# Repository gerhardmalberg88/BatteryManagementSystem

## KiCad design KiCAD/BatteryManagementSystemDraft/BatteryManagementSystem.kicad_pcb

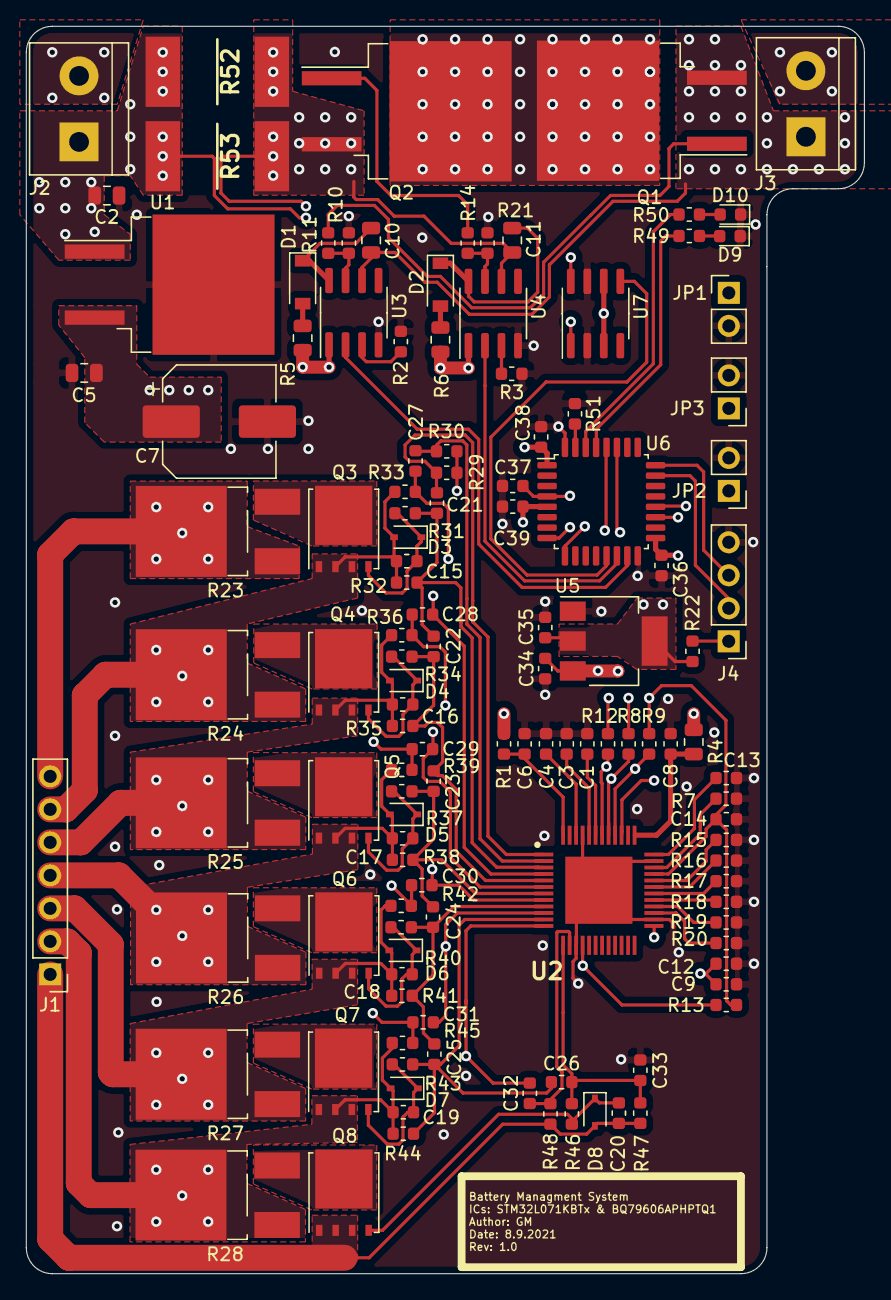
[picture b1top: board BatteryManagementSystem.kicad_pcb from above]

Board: 4 copper layers, 64.5 x 96.0 mm, 124 parts (0 on the bottom side), 82 nets.

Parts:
C1, C3, C4, C9, C12, C13, C14: 2.2uF 10V; C_0603_1608Metric
C2: 0.33uF; C_0805_2012Metric
C5: 0.1uF; C_0805_2012Metric
C6, C8: 330nF 50V; C_0603_1608Metric
C7: 100uF; CP_Elec_8x10.5
C10, C11: 1uF; C_0805_2012Metric
C15, C16, C17, C18, C19, C20: 1nF; C_0603_1608Metric
C21, C22, C23, C24, C25, C26, C27, C28, C29, C30, C31, C32: 1uF; C_0603_1608Metric
C33: 470nF 16V; C_0603_1608Metric
C34, C36, C38, C39: 100nF 10V; C_0603_1608Metric
C35: 10uF 10V; C_0603_1608Metric
C37: 0.1uF; C_0603_1608Metric
D1, D2: 1N6263W-7-F 1A; D_SOD-123
D3, D4, D5, D6, D7, D8: TVS_5.1V; D_SOD-323
D9, D10: LED; LED_0603_1608Metric
J1: Conn_01x07_Male; PinHeader_1x07_P2.54mm_Vertical
J2, J3: Screw_Terminal_01x02; TerminalBlock_bornier-2_P5.08mm
J4: Conn_01x04_Male; PinHeader_1x04_P2.54mm_Vertical
JP1, JP2, JP3: Jumper_2_Open; PinHeader_1x02_P2.54mm_Vertical
Q1, Q2: STB45N65M5 NMOS; TO-263-2
Q3, Q4, Q5, Q6, Q7, Q8: CSD16342Q5A; TDSON-8-1
R1, R11, R14, R29, R32, R35, R38, R41, R44, R47: 100R; R_0603_1608Metric
R2, R3, R7, R8, R9, R10, R12, R13, R21, R51: 100k; R_0603_1608Metric
R4: 49R; R_0805_2012Metric
R5, R6: 2R; R_0805_2012Metric
R15, R16, R17, R18, R19, R20, R49, R50: 10k; R_0603_1608Metric
R22: 0R; R_0603_1608Metric
R23, R24, R25, R26, R27, R28: 0R750; TO-252-2_TabPin1
R30, R33, R36, R39, R42, R45, R48: 400R; R_0603_1608Metric
R31, R34, R37, R40, R43, R46: 1k; R_0603_1608Metric
R52, R53: CSS2H-3920R-L200F; RESC10052X130N
U1: L7812CD2T; TO-263-2
U2: BQ79606APHPTQ1; QFP50P900X900X120-49N
U3, U4: LM5109BMA; SOIC-8_3.9x4.9mm_P1.27mm
U5: LD1117S33TR_SOT223; SOT-223-3_TabPin2
U6: STM32L071KBTx; LQFP-32_7x7mm_P0.8mm
U7: INA286; SOIC-8_3.9x4.9mm_P1.27mm

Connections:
+3V3: C35.2, C36.2, C38.2, C39.2, R22.2, U5.2, U6.1, U6.5, U6.17, U7.3, U7.6
/+12V: C5.2, C7.1, R5.2, R6.2, U1.3, U3.1, U4.1
/+25V2: C2.2, J1.7, J2.1, R1.2, R4.2, R23.1, R29.1, R30.1, R52.1, R53.1, U1.1, U7.8
/BalancingCircuit/CB0: C26.2, C33.1, R46.2, R47.2, U2.13
/BalancingCircuit/CB1: C25.2, C26.1, R43.2, R44.2, U2.11
/BalancingCircuit/CB2: C24.2, C25.1, R40.2, R41.2, U2.9
/BalancingCircuit/CB3: C23.2, C24.1, R37.2, R38.2, U2.7
/BalancingCircuit/CB4: C22.2, C23.1, R34.2, R35.2, U2.5
/BalancingCircuit/CB5: C21.2, C22.1, R31.2, R32.2, U2.3
/BalancingCircuit/CB6: C21.1, R29.2, U2.1
/BalancingCircuit/VC0: C32.2, R48.2, U2.14
/BalancingCircuit/VC1: C31.2, C32.1, R45.2, U2.12
/BalancingCircuit/VC2: C30.2, C31.1, R42.2, U2.10
/BalancingCircuit/VC3: C29.2, C30.1, R39.2, U2.8
/BalancingCircuit/VC4: C28.2, C29.1, R36.2, U2.6
/BalancingCircuit/VC5: C27.2, C28.1, R33.2, U2.4
/BalancingCircuit/VC6: C27.1, R30.2, U2.2
/BmsRX_McuTX: R8.1, U2.41, U6.20
/BmsTX_McuRX: R9.1, U2.40, U6.19
/CELL0: C20.2, D8.2, J1.1, Q8.1, Q8.2, Q8.3, R47.1, R48.1
/CELL1: C19.2, D7.2, J1.2, Q7.1, Q7.2, Q7.3, R28.1, R44.1, R45.1
/CELL2: C18.2, D6.2, J1.3, Q6.1, Q6.2, Q6.3, R27.1, R41.1, R42.1
/CELL3: C17.2, D5.2, J1.4, Q5.1, Q5.2, Q5.3, R26.1, R38.1, R39.1
/CELL4: C16.2, D4.2, J1.5, Q4.1, Q4.2, Q4.3, R25.1, R35.1, R36.1
/CELL5: C15.2, D3.2, J1.6, Q3.1, Q3.2, Q3.3, R24.1, R32.1, R33.1
/ChargeEnable: U4.2, U6.14
/DischargeEnable: U3.2, U6.15
/HOCharge: R14.1, R21.2, U4.7
/HODischarge: R10.2, R11.1, U3.7
/MCU/ExtraIndicatorOutput: R49.2, U6.29
/MCU/ExtraInput1: JP3.1, U6.8
/MCU/ExtraInput2: JP2.1, U6.9
/MCU/PowerUpIndicatorOutput: R50.2, U6.30
/MCU/SWCLK: J4.3, U6.24
/MCU/SWDIO: J4.2, U6.23
/MCU/Vcurrent: U6.13, U7.5
/NFAULT: R12.2, U2.42, U6.27
/VLDO: C9.2, C12.2, C34.2, U2.25, U2.39, U5.3
/VsCharge: C11.1, Q2.3, R52.2, R53.2, U4.6, U7.1
/VsDischarge: C10.1, J3.1, Q1.3, U3.6
/WAKEUP: R13.1, U2.16, U6.28
GND: C1.1, C2.1, C3.1, C4.1, C5.1, C6.1, C7.2, C8.1, C9.1, C12.1, C13.1, C14.1, C33.2, C34.1, C35.1, C36.1, C37.1, C38.1, C39.1, D9.1, D10.1, J2.2, J3.2, J4.4, JP1.2, JP2.2, JP3.2, R2.1, R3.1, R7.1, R10.1, R15.1, R16.1, R17.1, R18.1, R19.1, R20.1, R21.1, R51.1, U1.2, U2.15, U2.26, U2.35, U2.45, U2.49, U3.4, U4.4, U5.1, U6.16, U6.32, U7.2, U7.7
unnamed: C1.2, U2.43
unnamed: C3.2, U2.44
unnamed: C4.2, U2.46
unnamed: C6.2, R1.1, U2.48
unnamed: C8.2, R4.1, U2.37
unnamed: C10.2, D1.1, U3.8
unnamed: C11.2, D2.1, U4.8
unnamed: C13.2, U2.36
unnamed: C14.2, R8.2, R9.2, R12.1, R13.2, U2.33
unnamed: C15.1, D3.1, Q3.4, R31.1
unnamed: C16.1, D4.1, Q4.4, R34.1
unnamed: C17.1, D5.1, Q5.4, R37.1
unnamed: C18.1, D6.1, Q6.4, R40.1
unnamed: C19.1, D7.1, Q7.4, R43.1
unnamed: C20.1, D8.1, Q8.4, R46.1
unnamed: C37.2, JP1.1, U6.4
unnamed: D1.2, R5.1
unnamed: D2.2, R6.1
unnamed: D9.2, R49.1
unnamed: D10.2, R50.1
unnamed: J4.1, R22.1
unnamed: Q1.1, R11.2
unnamed: Q1.2, Q2.2
unnamed: Q2.1, R14.2
unnamed: Q3.5, R23.2
unnamed: Q4.5, R24.2
unnamed: Q5.5, R25.2
unnamed: Q6.5, R26.2
unnamed: Q7.5, R27.2
unnamed: Q8.5, R28.2
unnamed: R2.2, U3.3
unnamed: R3.2, U4.3
unnamed: R7.2, U2.34
unnamed: R15.2, U2.32
unnamed: R16.2, U2.31
unnamed: R17.2, U2.30
unnamed: R18.2, U2.29
unnamed: R19.2, U2.28
unnamed: R20.2, U2.27
unnamed: R51.2, U6.31

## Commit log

2021-08-31 Added initial KiCAD Files
2021-09-01 Updated Kicad Files
2021-09-07 Layout Update
2021-09-08 Updated Layout
2021-09-10 Added Shunt Current Measurement
2021-09-10 Added schematic PDF
2021-09-11 Layout main mosfet changes
